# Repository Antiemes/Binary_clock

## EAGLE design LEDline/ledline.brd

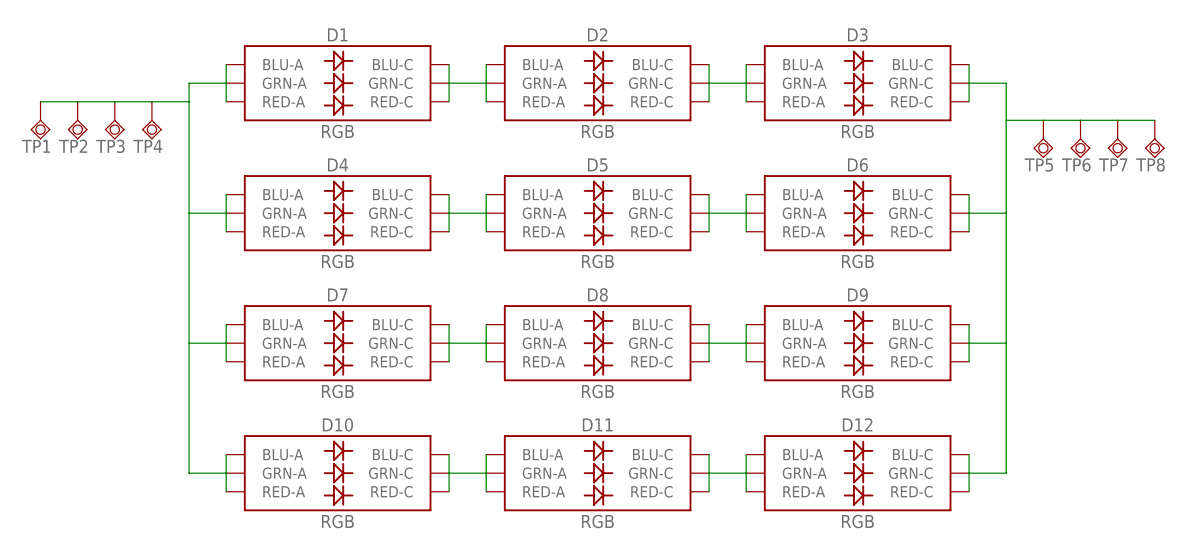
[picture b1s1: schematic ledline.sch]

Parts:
D1, D2, D3, D4, D5, D6, D7, D8, D9, D10, D11, D12: RGB; PLCC-6-LED
TP1, TP2, TP3, TP4, TP5, TP6, TP7, TP8: TPSQTP10SQ; TP10SQ

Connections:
GND: D3.CB (BLU-C), D3.CG (GRN-C), D3.CR (RED-C), D6.CB (BLU-C), D6.CG (GRN-C), D6.CR (RED-C), D9.CB (BLU-C), D9.CG (GRN-C), D9.CR (RED-C), D12.CB (BLU-C), D12.CG (GRN-C), D12.CR (RED-C), TP5.TP, TP6.TP, TP7.TP, TP8.TP
unnamed: D1.CB (BLU-C), D1.CG (GRN-C), D1.CR (RED-C), D2.AB (BLU-A), D2.AG (GRN-A), D2.AR (RED-A)
unnamed: D2.CB (BLU-C), D2.CG (GRN-C), D2.CR (RED-C), D3.AB (BLU-A), D3.AG (GRN-A), D3.AR (RED-A)
unnamed: D4.CB (BLU-C), D4.CG (GRN-C), D4.CR (RED-C), D5.AB (BLU-A), D5.AG (GRN-A), D5.AR (RED-A)
unnamed: D5.CB (BLU-C), D5.CG (GRN-C), D5.CR (RED-C), D6.AB (BLU-A), D6.AG (GRN-A), D6.AR (RED-A)
unnamed: D7.CB (BLU-C), D7.CG (GRN-C), D7.CR (RED-C), D8.AB (BLU-A), D8.AG (GRN-A), D8.AR (RED-A)
unnamed: D8.CB (BLU-C), D8.CG (GRN-C), D8.CR (RED-C), D9.AB (BLU-A), D9.AG (GRN-A), D9.AR (RED-A)
unnamed: D10.CB (BLU-C), D10.CG (GRN-C), D10.CR (RED-C), D11.AB (BLU-A), D11.AG (GRN-A), D11.AR (RED-A)
unnamed: D11.CB (BLU-C), D11.CG (GRN-C), D11.CR (RED-C), D12.AB (BLU-A), D12.AG (GRN-A), D12.AR (RED-A)
VCC: D1.AB (BLU-A), D1.AG (GRN-A), D1.AR (RED-A), D4.AB (BLU-A), D4.AG (GRN-A), D4.AR (RED-A), D7.AB (BLU-A), D7.AG (GRN-A), D7.AR (RED-A), D10.AB (BLU-A), D10.AG (GRN-A), D10.AR (RED-A), TP1.TP, TP2.TP, TP3.TP, TP4.TP

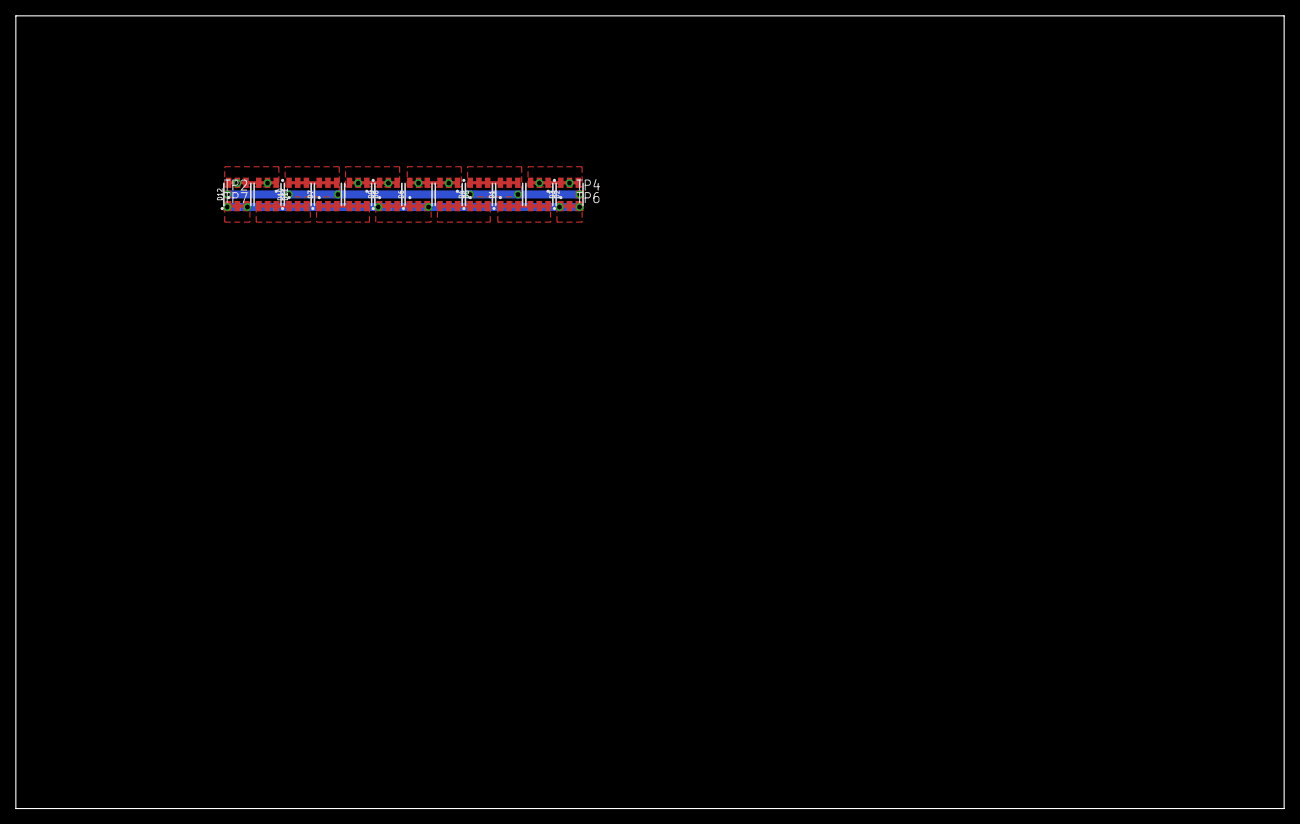
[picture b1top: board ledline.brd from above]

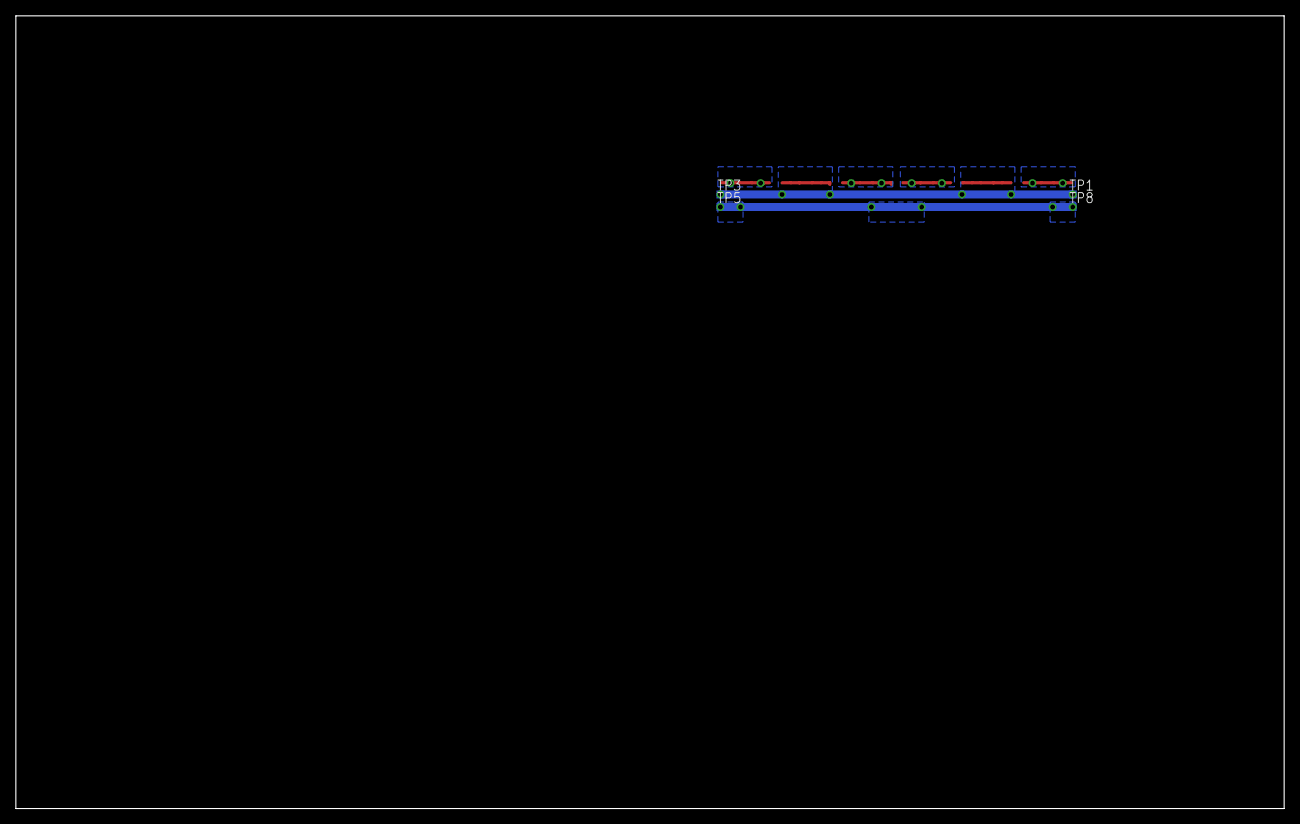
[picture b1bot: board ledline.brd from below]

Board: 2 copper layers, 160.0 x 100.0 mm, 20 parts (4 on the bottom side), 10 nets.

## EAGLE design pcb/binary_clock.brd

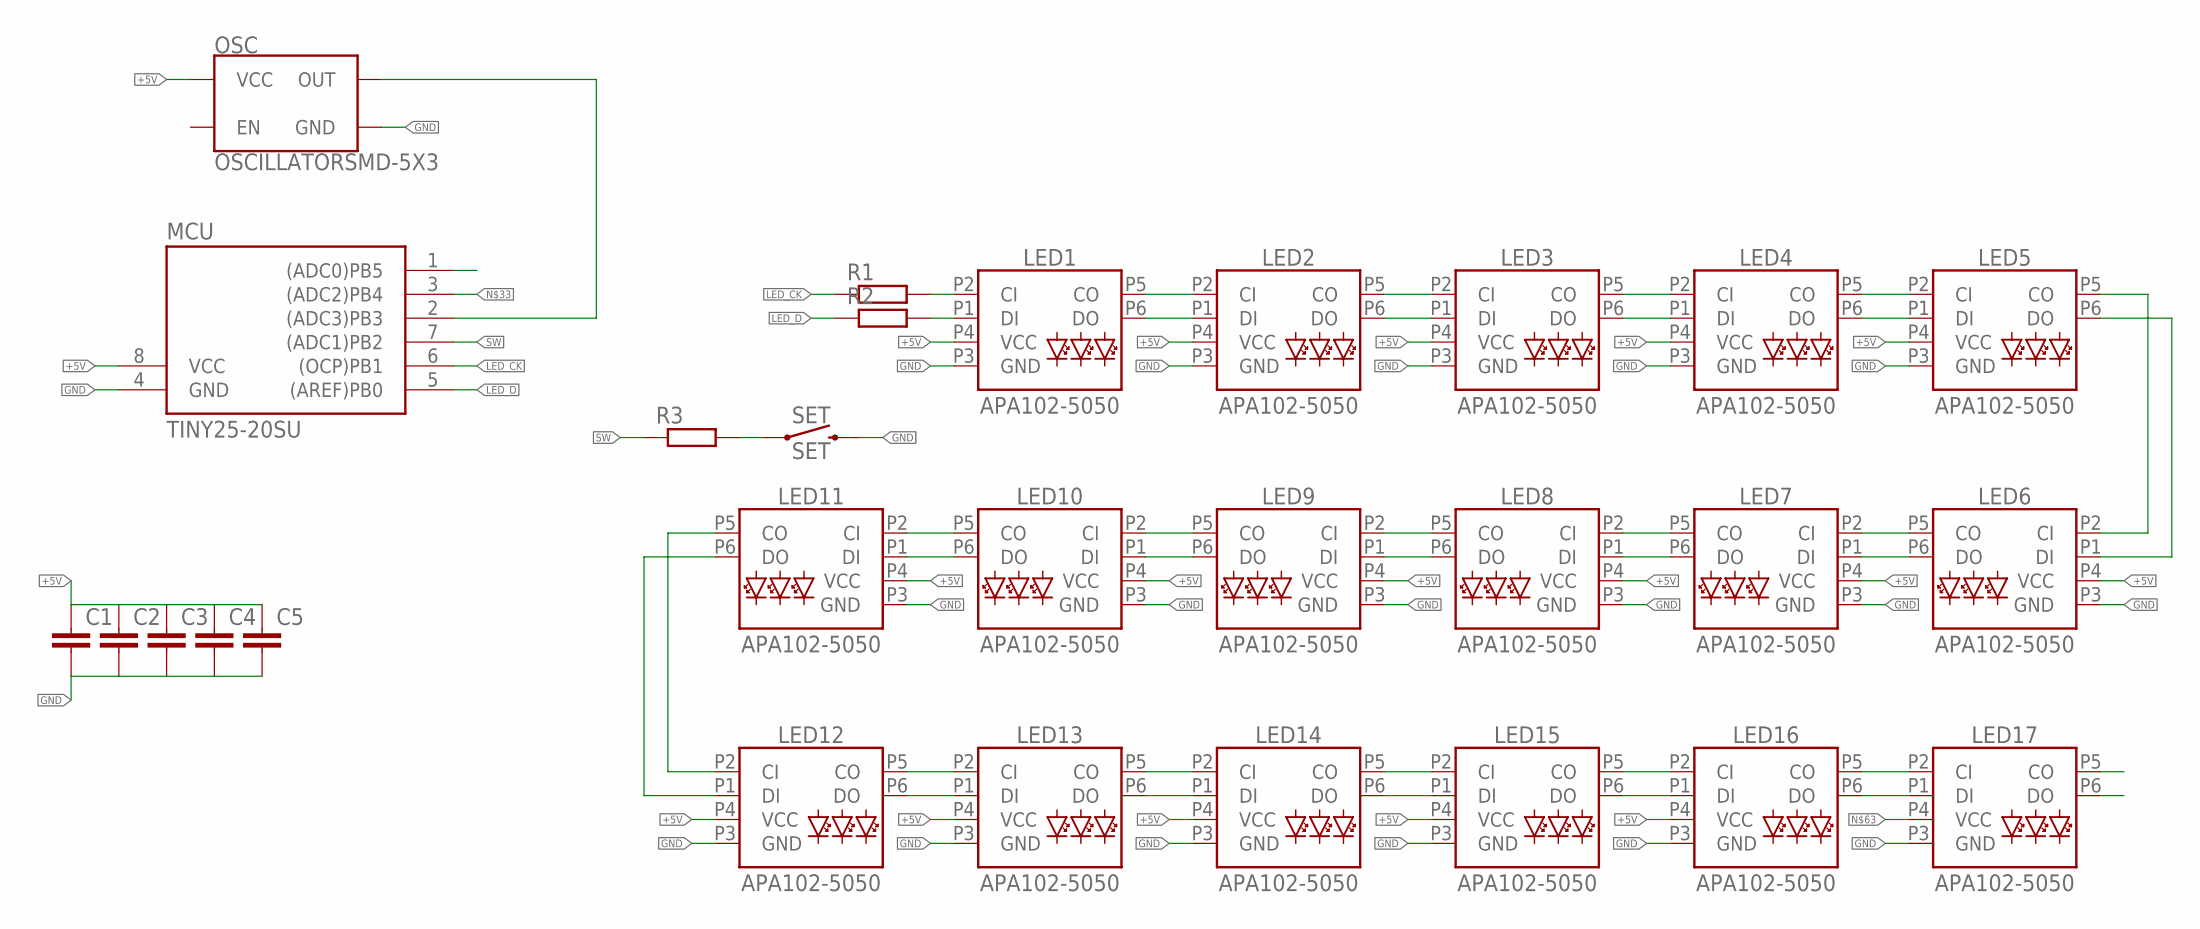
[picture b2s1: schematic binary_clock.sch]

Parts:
C1, C2, C3, C4, C5: C-EUC0603K; C0603K
LED1, LED2, LED3, LED4, LED5, LED6, LED7, LED8, LED9, LED10, LED11, LED12, LED13, LED14, LED15, LED16, LED17: APA102-5050
MCU: TINY25-20SU; SOIC8
OSC: OSCILLATORSMD-5X3; OSCILLATOR-SMD-5X3.2
R1, R2, R3: R-EU_R1206; R1206
SET: SET; TACTILE_SWITCH_SMD_5.2MM

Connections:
+5V: C1.1, C2.1, C3.1, C4.1, C5.1, LED1.P4 (VCC), LED2.P4 (VCC), LED3.P4 (VCC), LED4.P4 (VCC), LED5.P4 (VCC), LED6.P4 (VCC), LED7.P4 (VCC), LED8.P4 (VCC), LED9.P4 (VCC), LED10.P4 (VCC), LED11.P4 (VCC), LED12.P4 (VCC), LED13.P4 (VCC), LED14.P4 (VCC), LED15.P4 (VCC), LED16.P4 (VCC), MCU.8 (VCC), OSC.4 (VCC)
GND: C1.2, C2.2, C3.2, C4.2, C5.2, LED1.P3 (GND), LED2.P3 (GND), LED3.P3 (GND), LED4.P3 (GND), LED5.P3 (GND), LED6.P3 (GND), LED7.P3 (GND), LED8.P3 (GND), LED9.P3 (GND), LED10.P3 (GND), LED11.P3 (GND), LED12.P3 (GND), LED13.P3 (GND), LED14.P3 (GND), LED15.P3 (GND), LED16.P3 (GND), LED17.P3 (GND), MCU.4 (GND), OSC.2 (GND), SET.3 (2), SET.4 (2)
LED_CK: MCU.6 ((OCP)PB1), R1.1
LED_D: MCU.5 ((AREF)PB0), R2.1
unnamed: LED1.P5 (CO), LED2.P2 (CI)
unnamed: LED1.P6 (DO), LED2.P1 (DI)
unnamed: LED2.P5 (CO), LED3.P2 (CI)
unnamed: LED2.P6 (DO), LED3.P1 (DI)
unnamed: LED3.P5 (CO), LED4.P2 (CI)
unnamed: LED3.P6 (DO), LED4.P1 (DI)
unnamed: LED4.P5 (CO), LED5.P2 (CI)
unnamed: LED4.P6 (DO), LED5.P1 (DI)
unnamed: LED10.P5 (CO), LED11.P2 (CI)
unnamed: LED10.P6 (DO), LED11.P1 (DI)
unnamed: LED9.P6 (DO), LED10.P1 (DI)
unnamed: LED9.P5 (CO), LED10.P2 (CI)
unnamed: LED8.P6 (DO), LED9.P1 (DI)
unnamed: LED8.P5 (CO), LED9.P2 (CI)
unnamed: LED7.P6 (DO), LED8.P1 (DI)
unnamed: LED7.P5 (CO), LED8.P2 (CI)
unnamed: LED6.P6 (DO), LED7.P1 (DI)
unnamed: LED6.P5 (CO), LED7.P2 (CI)
unnamed: LED11.P6 (DO), LED12.P1 (DI)
unnamed: LED11.P5 (CO), LED12.P2 (CI)
unnamed: LED12.P5 (CO), LED13.P2 (CI)
unnamed: LED12.P6 (DO), LED13.P1 (DI)
unnamed: LED13.P5 (CO), LED14.P2 (CI)
unnamed: LED13.P6 (DO), LED14.P1 (DI)
unnamed: LED14.P5 (CO), LED15.P2 (CI)
unnamed: LED14.P6 (DO), LED15.P1 (DI)
unnamed: LED15.P5 (CO), LED16.P2 (CI)
unnamed: LED15.P6 (DO), LED16.P1 (DI)
unnamed: LED16.P5 (CO), LED17.P2 (CI)
unnamed: LED16.P6 (DO), LED17.P1 (DI)
unnamed: MCU.2 ((ADC3)PB3), OSC.3 (OUT)
unnamed: R3.2, SET.1, SET.2 (1)
unnamed: LED5.P6 (DO), LED6.P1 (DI)
unnamed: LED5.P5 (CO), LED6.P2 (CI)
unnamed: LED1.P1 (DI), R2.2
unnamed: LED1.P2 (CI), R1.2
SW: MCU.7 ((ADC1)PB2), R3.1

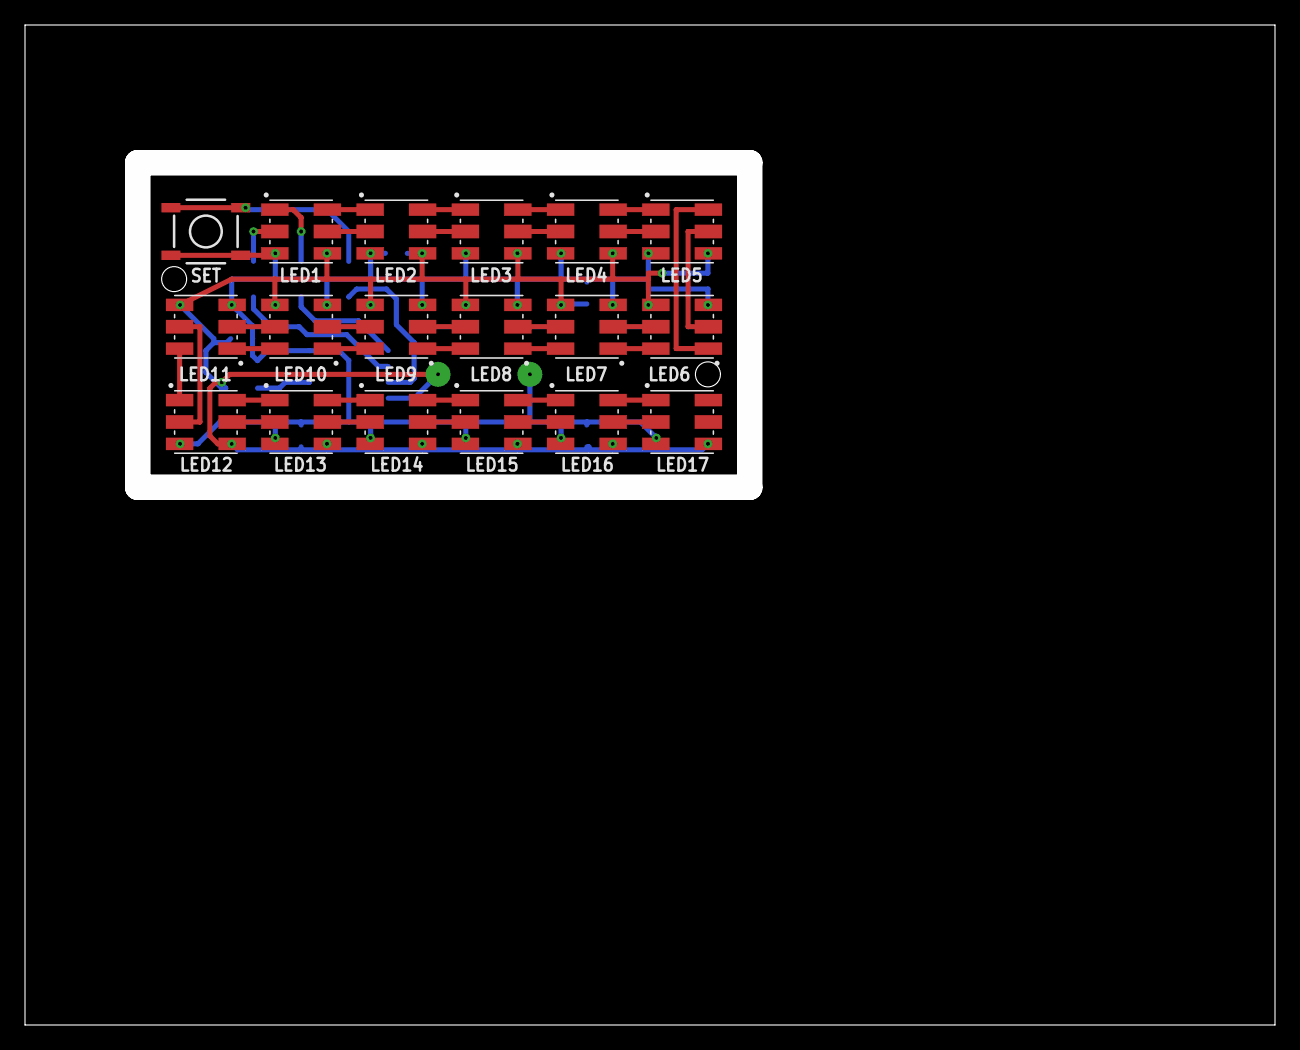
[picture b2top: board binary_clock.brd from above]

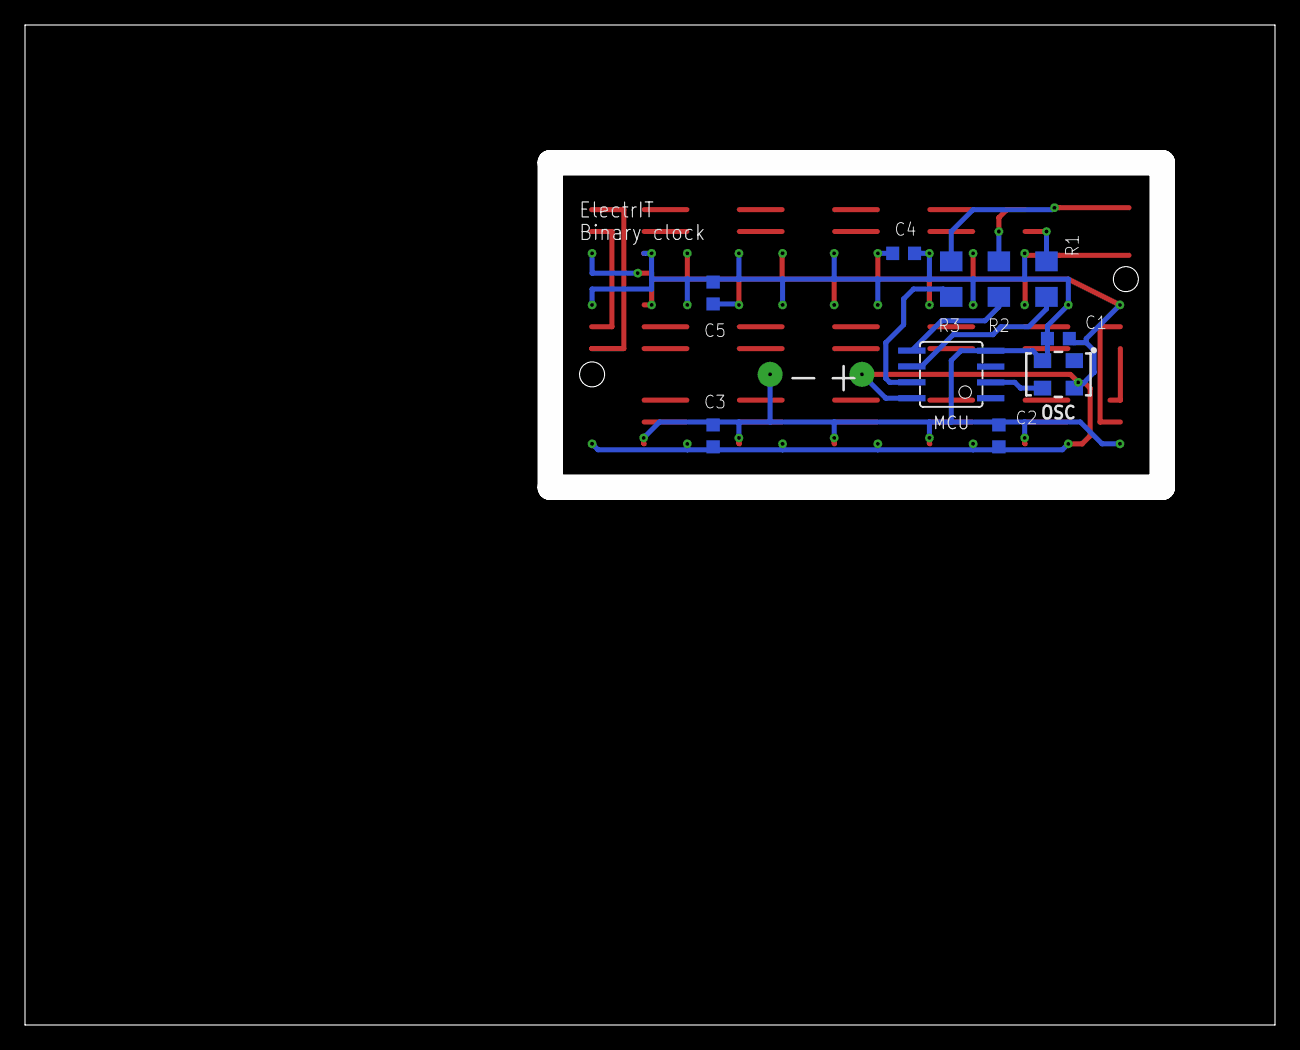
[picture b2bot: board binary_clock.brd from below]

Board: 2 copper layers, 100.0 x 80.0 mm, 28 parts (10 on the bottom side), 41 nets.

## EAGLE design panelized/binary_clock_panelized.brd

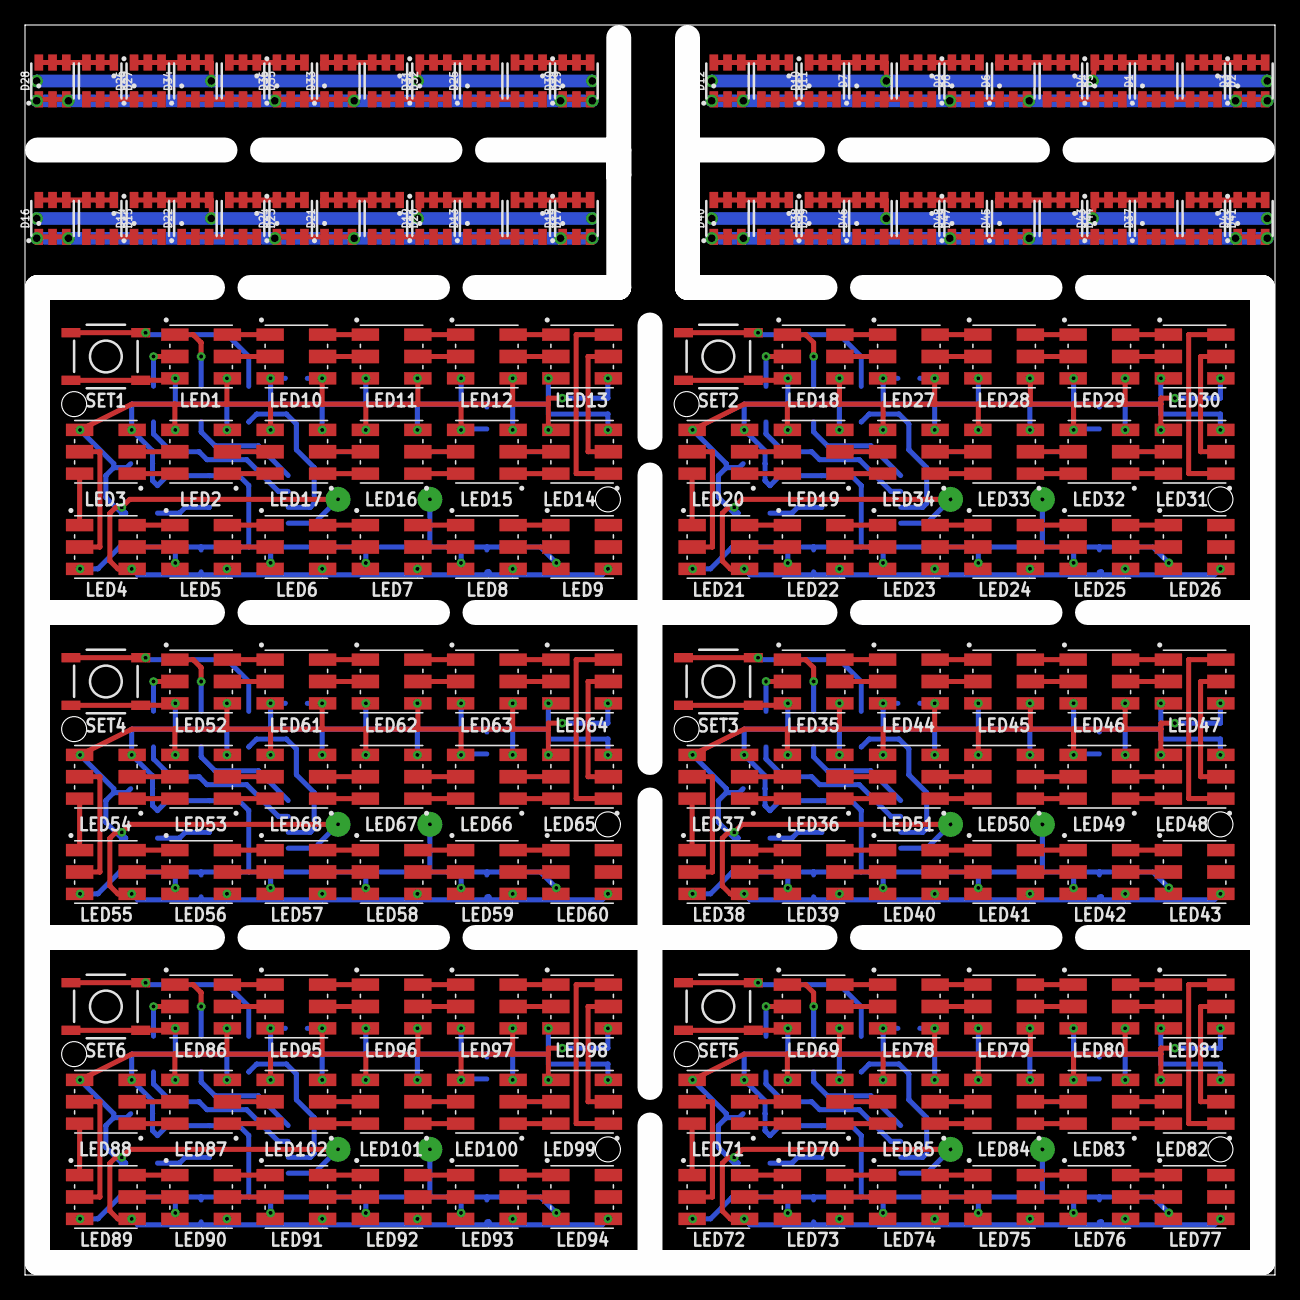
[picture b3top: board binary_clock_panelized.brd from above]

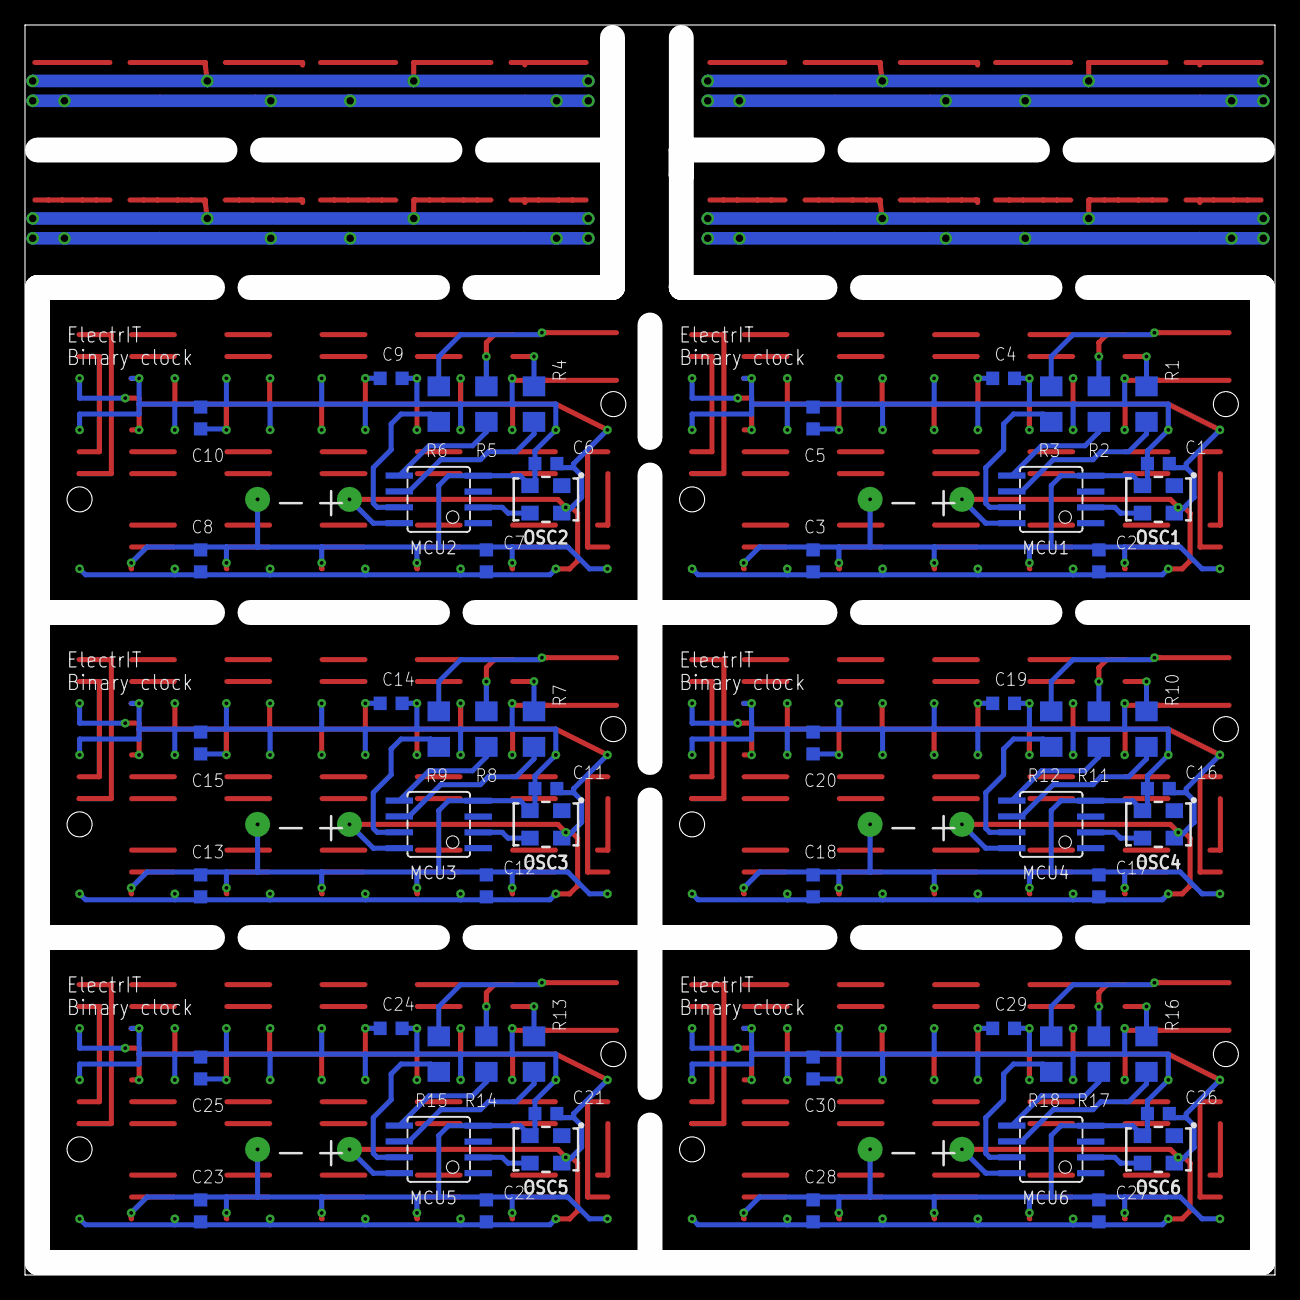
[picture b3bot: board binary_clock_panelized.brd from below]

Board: 2 copper layers, 100.0 x 100.0 mm, 216 parts (60 on the bottom side), 286 nets.

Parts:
C1, C2, C3, C4, C5, C6, C7, C8, C9, C10, C11, C12, C13, C14, C15, C16, C17, C18, C19, C20, C21, C22, C23, C24, C25, C26, C27, C28, C29, C30: C0603K
D1, D2, D3, D4, D5, D6, D7, D8, D9, D10, D11, D12, D13, D14, D15, D16, D17, D18, D19, D20, D21, D22, D23, D24, D25, D26, D27, D28, D29, D30, D31, D32, D33, D34, D35, D36, D37, D38, D39, D40, D41, D42, D43, D44, D45, D46, D47, D48: RGB; PLCC-6-LED
LED1, LED2, LED3, LED4, LED5, LED6, LED7, LED8, LED9, LED10, LED11, LED12, LED13, LED14, LED15, LED16, LED17, LED18, LED19, LED20, LED21, LED22, LED23, LED24, LED25, LED26, LED27, LED28, LED29, LED30, LED31, LED32, LED33, LED34, LED35, LED36, LED37, LED38, LED39, LED40, LED41, LED42, LED43, LED44, LED45, LED46, LED47, LED48, LED49, LED50, LED51, LED52, LED53, LED54, LED55, LED56, LED57, LED58, LED59, LED60, LED61, LED62, LED63, LED64, LED65, LED66, LED67, LED68, LED69, LED70, LED71, LED72, LED73, LED74, LED75, LED76, LED77, LED78, LED79, LED80, LED81, LED82, LED83, LED84, LED85, LED86, LED87, LED88, LED89, LED90, LED91, LED92, LED93, LED94, LED95, LED96, LED97, LED98, LED99, LED100, LED101, LED102: APA102-5050
MCU1, MCU2, MCU3, MCU4, MCU5, MCU6: TINY25-20SU; SOIC8
OSC1, OSC2, OSC3, OSC4, OSC5, OSC6: OSCILLATORSMD-5X3; OSCILLATOR-SMD-5X3.2
R1, R2, R3, R4, R5, R6, R7, R8, R9, R10, R11, R12, R13, R14, R15, R16, R17, R18: R1206
SET1, SET2, SET3, SET4, SET5, SET6: SET; TACTILE_SWITCH_SMD_5.2MM

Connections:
+5V1: C1.1, C2.1, C3.1, C4.1, C5.1, LED1.P4, LED2.P4, LED3.P4, LED4.P4, LED5.P4, LED6.P4, LED7.P4, LED8.P4, LED10.P4, LED11.P4, LED12.P4, LED13.P4, LED14.P4, LED15.P4, LED16.P4, LED17.P4, MCU1.8, OSC1.4
+5V2: C6.1, C7.1, C8.1, C9.1, C10.1, LED18.P4, LED19.P4, LED20.P4, LED21.P4, LED22.P4, LED23.P4, LED24.P4, LED25.P4, LED27.P4, LED28.P4, LED29.P4, LED30.P4, LED31.P4, LED32.P4, LED33.P4, LED34.P4, MCU2.8, OSC2.4
+5V3: C11.1, C12.1, C13.1, C14.1, C15.1, LED35.P4, LED36.P4, LED37.P4, LED38.P4, LED39.P4, LED40.P4, LED41.P4, LED42.P4, LED44.P4, LED45.P4, LED46.P4, LED47.P4, LED48.P4, LED49.P4, LED50.P4, LED51.P4, MCU3.8, OSC3.4
+5V4: C16.1, C17.1, C18.1, C19.1, C20.1, LED52.P4, LED53.P4, LED54.P4, LED55.P4, LED56.P4, LED57.P4, LED58.P4, LED59.P4, LED61.P4, LED62.P4, LED63.P4, LED64.P4, LED65.P4, LED66.P4, LED67.P4, LED68.P4, MCU4.8, OSC4.4
+5V5: C21.1, C22.1, C23.1, C24.1, C25.1, LED69.P4, LED70.P4, LED71.P4, LED72.P4, LED73.P4, LED74.P4, LED75.P4, LED76.P4, LED78.P4, LED79.P4, LED80.P4, LED81.P4, LED82.P4, LED83.P4, LED84.P4, LED85.P4, MCU5.8, OSC5.4
+5V6: C26.1, C27.1, C28.1, C29.1, C30.1, LED86.P4, LED87.P4, LED88.P4, LED89.P4, LED90.P4, LED91.P4, LED92.P4, LED93.P4, LED95.P4, LED96.P4, LED97.P4, LED98.P4, LED99.P4, LED100.P4, LED101.P4, LED102.P4, MCU6.8, OSC6.4
GND1: C1.2, C2.2, C3.2, C4.2, C5.2, LED1.P3, LED2.P3, LED3.P3, LED4.P3, LED5.P3, LED6.P3, LED7.P3, LED8.P3, LED9.P3, LED10.P3, LED11.P3, LED12.P3, LED13.P3, LED14.P3, LED15.P3, LED16.P3, LED17.P3, MCU1.4, OSC1.2, SET1.3, SET1.4
GND2: C6.2, C7.2, C8.2, C9.2, C10.2, LED18.P3, LED19.P3, LED20.P3, LED21.P3, LED22.P3, LED23.P3, LED24.P3, LED25.P3, LED26.P3, LED27.P3, LED28.P3, LED29.P3, LED30.P3, LED31.P3, LED32.P3, LED33.P3, LED34.P3, MCU2.4, OSC2.2, SET2.3, SET2.4
GND3: C11.2, C12.2, C13.2, C14.2, C15.2, LED35.P3, LED36.P3, LED37.P3, LED38.P3, LED39.P3, LED40.P3, LED41.P3, LED42.P3, LED43.P3, LED44.P3, LED45.P3, LED46.P3, LED47.P3, LED48.P3, LED49.P3, LED50.P3, LED51.P3, MCU3.4, OSC3.2, SET3.3, SET3.4
GND4: C16.2, C17.2, C18.2, C19.2, C20.2, LED52.P3, LED53.P3, LED54.P3, LED55.P3, LED56.P3, LED57.P3, LED58.P3, LED59.P3, LED60.P3, LED61.P3, LED62.P3, LED63.P3, LED64.P3, LED65.P3, LED66.P3, LED67.P3, LED68.P3, MCU4.4, OSC4.2, SET4.3, SET4.4
GND5: C21.2, C22.2, C23.2, C24.2, C25.2, LED69.P3, LED70.P3, LED71.P3, LED72.P3, LED73.P3, LED74.P3, LED75.P3, LED76.P3, LED77.P3, LED78.P3, LED79.P3, LED80.P3, LED81.P3, LED82.P3, LED83.P3, LED84.P3, LED85.P3, MCU5.4, OSC5.2, SET5.3, SET5.4
GND6: C26.2, C27.2, C28.2, C29.2, C30.2, LED86.P3, LED87.P3, LED88.P3, LED89.P3, LED90.P3, LED91.P3, LED92.P3, LED93.P3, LED94.P3, LED95.P3, LED96.P3, LED97.P3, LED98.P3, LED99.P3, LED100.P3, LED101.P3, LED102.P3, MCU6.4, OSC6.2, SET6.3, SET6.4
GND7: D3.CB, D3.CG, D3.CR, D6.CB, D6.CG, D6.CR, D9.CB, D9.CG, D9.CR, D12.CB, D12.CG, D12.CR
GND8: D16.CB, D16.CG, D16.CR, D18.CB, D18.CG, D18.CR, D21.CB, D21.CG, D21.CR, D24.CB, D24.CG, D24.CR
GND9: D28.CB, D28.CG, D28.CR, D30.CB, D30.CG, D30.CR, D33.CB, D33.CG, D33.CR, D36.CB, D36.CG, D36.CR
GND10: D40.CB, D40.CG, D40.CR, D42.CB, D42.CG, D42.CR, D45.CB, D45.CG, D45.CR, D48.CB, D48.CG, D48.CR
LED_CK1: MCU1.6, R1.1
LED_CK2: MCU2.6, R4.1
LED_CK3: MCU3.6, R7.1
LED_CK4: MCU4.6, R10.1
LED_CK5: MCU5.6, R13.1
LED_CK6: MCU6.6, R16.1
LED_D1: MCU1.5, R2.1
LED_D2: MCU2.5, R5.1
LED_D3: MCU3.5, R8.1
LED_D4: MCU4.5, R11.1
LED_D5: MCU5.5, R14.1
LED_D6: MCU6.5, R17.1
unnamed: LED1.P5, LED10.P2
unnamed: LED1.P6, LED10.P1
unnamed: LED10.P5, LED11.P2
unnamed: LED10.P6, LED11.P1
unnamed: LED11.P5, LED12.P2
unnamed: LED11.P6, LED12.P1
unnamed: LED12.P5, LED13.P2
unnamed: LED12.P6, LED13.P1
unnamed: LED4.P5, LED5.P2
unnamed: LED4.P6, LED5.P1
unnamed: LED5.P5, LED6.P2
unnamed: LED5.P6, LED6.P1
unnamed: LED6.P5, LED7.P2
unnamed: LED6.P6, LED7.P1
unnamed: LED7.P5, LED8.P2
unnamed: LED7.P6, LED8.P1
unnamed: LED8.P5, LED9.P2
unnamed: LED8.P6, LED9.P1
unnamed: LED2.P5, LED3.P2
unnamed: LED2.P6, LED3.P1
unnamed: LED2.P1, LED17.P6
unnamed: LED2.P2, LED17.P5
unnamed: LED16.P6, LED17.P1
unnamed: LED16.P5, LED17.P2
unnamed: LED15.P6, LED16.P1
unnamed: LED15.P5, LED16.P2
unnamed: LED14.P6, LED15.P1
unnamed: LED14.P5, LED15.P2
unnamed: LED3.P6, LED4.P1
unnamed: LED3.P5, LED4.P2
unnamed: LED13.P6, LED14.P1
unnamed: LED1.P1, R2.2
unnamed: LED1.P2, R1.2
unnamed: LED13.P5, LED14.P2
unnamed: MCU1.2, OSC1.3
unnamed: R3.2, SET1.1, SET1.2
unnamed: LED18.P5, LED27.P2
unnamed: LED18.P6, LED27.P1
unnamed: LED27.P5, LED28.P2
unnamed: LED27.P6, LED28.P1
unnamed: LED28.P5, LED29.P2
unnamed: LED28.P6, LED29.P1
unnamed: LED29.P5, LED30.P2
unnamed: LED29.P6, LED30.P1
unnamed: LED21.P5, LED22.P2
unnamed: LED21.P6, LED22.P1
unnamed: LED22.P5, LED23.P2
unnamed: LED22.P6, LED23.P1
unnamed: LED23.P5, LED24.P2
unnamed: LED23.P6, LED24.P1
unnamed: LED24.P5, LED25.P2
unnamed: LED24.P6, LED25.P1
unnamed: LED25.P5, LED26.P2
unnamed: LED25.P6, LED26.P1
unnamed: LED19.P5, LED20.P2
unnamed: LED19.P6, LED20.P1
unnamed: LED19.P1, LED34.P6
unnamed: LED19.P2, LED34.P5
unnamed: LED33.P6, LED34.P1
unnamed: LED33.P5, LED34.P2
unnamed: LED32.P6, LED33.P1
unnamed: LED32.P5, LED33.P2
unnamed: LED31.P6, LED32.P1
unnamed: LED31.P5, LED32.P2
unnamed: LED20.P6, LED21.P1
unnamed: LED20.P5, LED21.P2
unnamed: LED30.P6, LED31.P1
unnamed: LED18.P1, R5.2
unnamed: LED18.P2, R4.2
unnamed: LED30.P5, LED31.P2
unnamed: MCU2.2, OSC2.3
unnamed: R6.2, SET2.1, SET2.2
unnamed: LED35.P5, LED44.P2
unnamed: LED35.P6, LED44.P1
unnamed: LED44.P5, LED45.P2
unnamed: LED44.P6, LED45.P1
unnamed: LED45.P5, LED46.P2
unnamed: LED45.P6, LED46.P1
unnamed: LED46.P5, LED47.P2
unnamed: LED46.P6, LED47.P1
unnamed: LED38.P5, LED39.P2
unnamed: LED38.P6, LED39.P1
unnamed: LED39.P5, LED40.P2
unnamed: LED39.P6, LED40.P1
unnamed: LED40.P5, LED41.P2
unnamed: LED40.P6, LED41.P1
unnamed: LED41.P5, LED42.P2
unnamed: LED41.P6, LED42.P1
unnamed: LED42.P5, LED43.P2
unnamed: LED42.P6, LED43.P1
unnamed: LED36.P5, LED37.P2
unnamed: LED36.P6, LED37.P1
unnamed: LED36.P1, LED51.P6
unnamed: LED36.P2, LED51.P5
unnamed: LED50.P6, LED51.P1
unnamed: LED50.P5, LED51.P2
unnamed: LED49.P6, LED50.P1
unnamed: LED49.P5, LED50.P2
unnamed: LED48.P6, LED49.P1
unnamed: LED48.P5, LED49.P2
unnamed: LED37.P6, LED38.P1
unnamed: LED37.P5, LED38.P2
unnamed: LED47.P6, LED48.P1
unnamed: LED35.P1, R8.2
unnamed: LED35.P2, R7.2
unnamed: LED47.P5, LED48.P2
unnamed: MCU3.2, OSC3.3
unnamed: R9.2, SET3.1, SET3.2
unnamed: LED52.P5, LED61.P2
unnamed: LED52.P6, LED61.P1
unnamed: LED61.P5, LED62.P2
unnamed: LED61.P6, LED62.P1
unnamed: LED62.P5, LED63.P2
unnamed: LED62.P6, LED63.P1
unnamed: LED63.P5, LED64.P2
unnamed: LED63.P6, LED64.P1
unnamed: LED55.P5, LED56.P2
unnamed: LED55.P6, LED56.P1
unnamed: LED56.P5, LED57.P2
unnamed: LED56.P6, LED57.P1
unnamed: LED57.P5, LED58.P2
unnamed: LED57.P6, LED58.P1
unnamed: LED58.P5, LED59.P2
unnamed: LED58.P6, LED59.P1
unnamed: LED59.P5, LED60.P2
unnamed: LED59.P6, LED60.P1
unnamed: LED53.P5, LED54.P2
unnamed: LED53.P6, LED54.P1
unnamed: LED53.P1, LED68.P6
unnamed: LED53.P2, LED68.P5
unnamed: LED67.P6, LED68.P1
unnamed: LED67.P5, LED68.P2
unnamed: LED66.P6, LED67.P1
unnamed: LED66.P5, LED67.P2
unnamed: LED65.P6, LED66.P1
unnamed: LED65.P5, LED66.P2
unnamed: LED54.P6, LED55.P1
unnamed: LED54.P5, LED55.P2
unnamed: LED64.P6, LED65.P1
unnamed: LED52.P1, R11.2
unnamed: LED52.P2, R10.2
unnamed: LED64.P5, LED65.P2
unnamed: MCU4.2, OSC4.3
unnamed: R12.2, SET4.1, SET4.2
unnamed: LED69.P5, LED78.P2
unnamed: LED69.P6, LED78.P1
unnamed: LED78.P5, LED79.P2
unnamed: LED78.P6, LED79.P1
unnamed: LED79.P5, LED80.P2
unnamed: LED79.P6, LED80.P1
unnamed: LED80.P5, LED81.P2
unnamed: LED80.P6, LED81.P1
unnamed: LED72.P5, LED73.P2
unnamed: LED72.P6, LED73.P1
unnamed: LED73.P5, LED74.P2
unnamed: LED73.P6, LED74.P1
unnamed: LED74.P5, LED75.P2
unnamed: LED74.P6, LED75.P1
unnamed: LED75.P5, LED76.P2
unnamed: LED75.P6, LED76.P1
unnamed: LED76.P5, LED77.P2
unnamed: LED76.P6, LED77.P1
unnamed: LED70.P5, LED71.P2
unnamed: LED70.P6, LED71.P1
unnamed: LED70.P1, LED85.P6
unnamed: LED70.P2, LED85.P5
unnamed: LED84.P6, LED85.P1
unnamed: LED84.P5, LED85.P2
unnamed: LED83.P6, LED84.P1
unnamed: LED83.P5, LED84.P2
unnamed: LED82.P6, LED83.P1
unnamed: LED82.P5, LED83.P2
unnamed: LED71.P6, LED72.P1
unnamed: LED71.P5, LED72.P2
unnamed: LED81.P6, LED82.P1
unnamed: LED69.P1, R14.2
unnamed: LED69.P2, R13.2
unnamed: LED81.P5, LED82.P2
unnamed: MCU5.2, OSC5.3
unnamed: R15.2, SET5.1, SET5.2
unnamed: LED86.P5, LED95.P2
unnamed: LED86.P6, LED95.P1
unnamed: LED95.P5, LED96.P2
unnamed: LED95.P6, LED96.P1
unnamed: LED96.P5, LED97.P2
unnamed: LED96.P6, LED97.P1
unnamed: LED97.P5, LED98.P2
unnamed: LED97.P6, LED98.P1
unnamed: LED89.P5, LED90.P2
unnamed: LED89.P6, LED90.P1
unnamed: LED90.P5, LED91.P2
unnamed: LED90.P6, LED91.P1
unnamed: LED91.P5, LED92.P2
unnamed: LED91.P6, LED92.P1
unnamed: LED92.P5, LED93.P2
unnamed: LED92.P6, LED93.P1
unnamed: LED93.P5, LED94.P2
unnamed: LED93.P6, LED94.P1
unnamed: LED87.P5, LED88.P2
unnamed: LED87.P6, LED88.P1
unnamed: LED87.P1, LED102.P6
unnamed: LED87.P2, LED102.P5
unnamed: LED101.P6, LED102.P1
unnamed: LED101.P5, LED102.P2
unnamed: LED100.P6, LED101.P1
unnamed: LED100.P5, LED101.P2
unnamed: LED99.P6, LED100.P1
unnamed: LED99.P5, LED100.P2
unnamed: LED88.P6, LED89.P1
unnamed: LED88.P5, LED89.P2
unnamed: LED98.P6, LED99.P1
unnamed: LED86.P1, R17.2
unnamed: LED86.P2, R16.2
unnamed: LED98.P5, LED99.P2
unnamed: MCU6.2, OSC6.3
unnamed: R18.2, SET6.1, SET6.2
unnamed: D1.CB, D1.CG, D1.CR, D2.AB, D2.AG, D2.AR
unnamed: D2.CB, D2.CG, D2.CR, D3.AB, D3.AG, D3.AR
unnamed: D4.CB, D4.CG, D4.CR, D5.AB, D5.AG, D5.AR
unnamed: D5.CB, D5.CG, D5.CR, D6.AB, D6.AG, D6.AR
unnamed: D7.CB, D7.CG, D7.CR, D8.AB, D8.AG, D8.AR
unnamed: D8.CB, D8.CG, D8.CR, D9.AB, D9.AG, D9.AR
unnamed: D10.CB, D10.CG, D10.CR, D11.AB, D11.AG, D11.AR
unnamed: D11.CB, D11.CG, D11.CR, D12.AB, D12.AG, D12.AR
unnamed: D13.CB, D13.CG, D13.CR, D17.AB, D17.AG, D17.AR
unnamed: D17.CB, D17.CG, D17.CR, D18.AB, D18.AG, D18.AR
unnamed: D19.CB, D19.CG, D19.CR, D20.AB, D20.AG, D20.AR
unnamed: D20.CB, D20.CG, D20.CR, D21.AB, D21.AG, D21.AR
unnamed: D22.CB, D22.CG, D22.CR, D23.AB, D23.AG, D23.AR
unnamed: D23.CB, D23.CG, D23.CR, D24.AB, D24.AG, D24.AR
unnamed: D14.CB, D14.CG, D14.CR, D15.AB, D15.AG, D15.AR
unnamed: D15.CB, D15.CG, D15.CR, D16.AB, D16.AG, D16.AR
unnamed: D25.CB, D25.CG, D25.CR, D29.AB, D29.AG, D29.AR
unnamed: D29.CB, D29.CG, D29.CR, D30.AB, D30.AG, D30.AR
unnamed: D31.CB, D31.CG, D31.CR, D32.AB, D32.AG, D32.AR
unnamed: D32.CB, D32.CG, D32.CR, D33.AB, D33.AG, D33.AR
unnamed: D34.CB, D34.CG, D34.CR, D35.AB, D35.AG, D35.AR
unnamed: D35.CB, D35.CG, D35.CR, D36.AB, D36.AG, D36.AR
unnamed: D26.CB, D26.CG, D26.CR, D27.AB, D27.AG, D27.AR
unnamed: D27.CB, D27.CG, D27.CR, D28.AB, D28.AG, D28.AR
unnamed: D37.CB, D37.CG, D37.CR, D41.AB, D41.AG, D41.AR
unnamed: D41.CB, D41.CG, D41.CR, D42.AB, D42.AG, D42.AR
unnamed: D43.CB, D43.CG, D43.CR, D44.AB, D44.AG, D44.AR
unnamed: D44.CB, D44.CG, D44.CR, D45.AB, D45.AG, D45.AR
unnamed: D46.CB, D46.CG, D46.CR, D47.AB, D47.AG, D47.AR
unnamed: D47.CB, D47.CG, D47.CR, D48.AB, D48.AG, D48.AR
unnamed: D38.CB, D38.CG, D38.CR, D39.AB, D39.AG, D39.AR
unnamed: D39.CB, D39.CG, D39.CR, D40.AB, D40.AG, D40.AR
SW1: MCU1.7, R3.1
SW2: MCU2.7, R6.1
SW3: MCU3.7, R9.1
SW4: MCU4.7, R12.1
SW5: MCU5.7, R15.1
SW6: MCU6.7, R18.1
VCC: D1.AB, D1.AG, D1.AR, D4.AB, D4.AG, D4.AR, D7.AB, D7.AG, D7.AR, D10.AB, D10.AG, D10.AR
VCC1: D13.AB, D13.AG, D13.AR, D14.AB, D14.AG, D14.AR, D19.AB, D19.AG, D19.AR, D22.AB, D22.AG, D22.AR
VCC2: D25.AB, D25.AG, D25.AR, D26.AB, D26.AG, D26.AR, D31.AB, D31.AG, D31.AR, D34.AB, D34.AG, D34.AR
VCC3: D37.AB, D37.AG, D37.AR, D38.AB, D38.AG, D38.AR, D43.AB, D43.AG, D43.AR, D46.AB, D46.AG, D46.AR

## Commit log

2019-01-11 Libs added
2019-01-11 PCB almost done.
2019-01-11 Switch connected
2019-01-11 Xtal library added.
2019-01-11 Routing done.
2019-01-11 Removed backup files.
2019-01-13 Silkscreen and resistor sizes
2019-01-17 Switch renamed
2019-01-17 More 100nFs added, short circuit corrected, text added
2019-01-24 LED line added
2019-01-24 Binary clock and LED line panelized
2019-01-25 Font sizes and positions corrected
2019-01-25 Panelized version corrected
2019-01-25 CAM job file added
2019-01-25 Heatsink and testpad added
2019-01-25 MOAAAAR heatsink
2019-04-26 Does not work yet...
2019-04-26 LEDS seem to work
2019-04-26 Basic functionality, no time setting.
2019-04-28 Color selector modified, button support added
2019-04-30 Enclosure far from done
2019-04-30 Almost done
2019-04-30 Maybe done
2019-05-01 LEDline removed
2019-05-02 Warning corrected, battery model removed

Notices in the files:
parts and their libraries:
SparkFun-LED: Licensing: Creative Commons ShareAlike 4.0 International - https://creativecommons.org/licenses/by-sa/4.0
